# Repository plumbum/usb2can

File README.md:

usb2can
=======

USB/Serial to CAN bus converter

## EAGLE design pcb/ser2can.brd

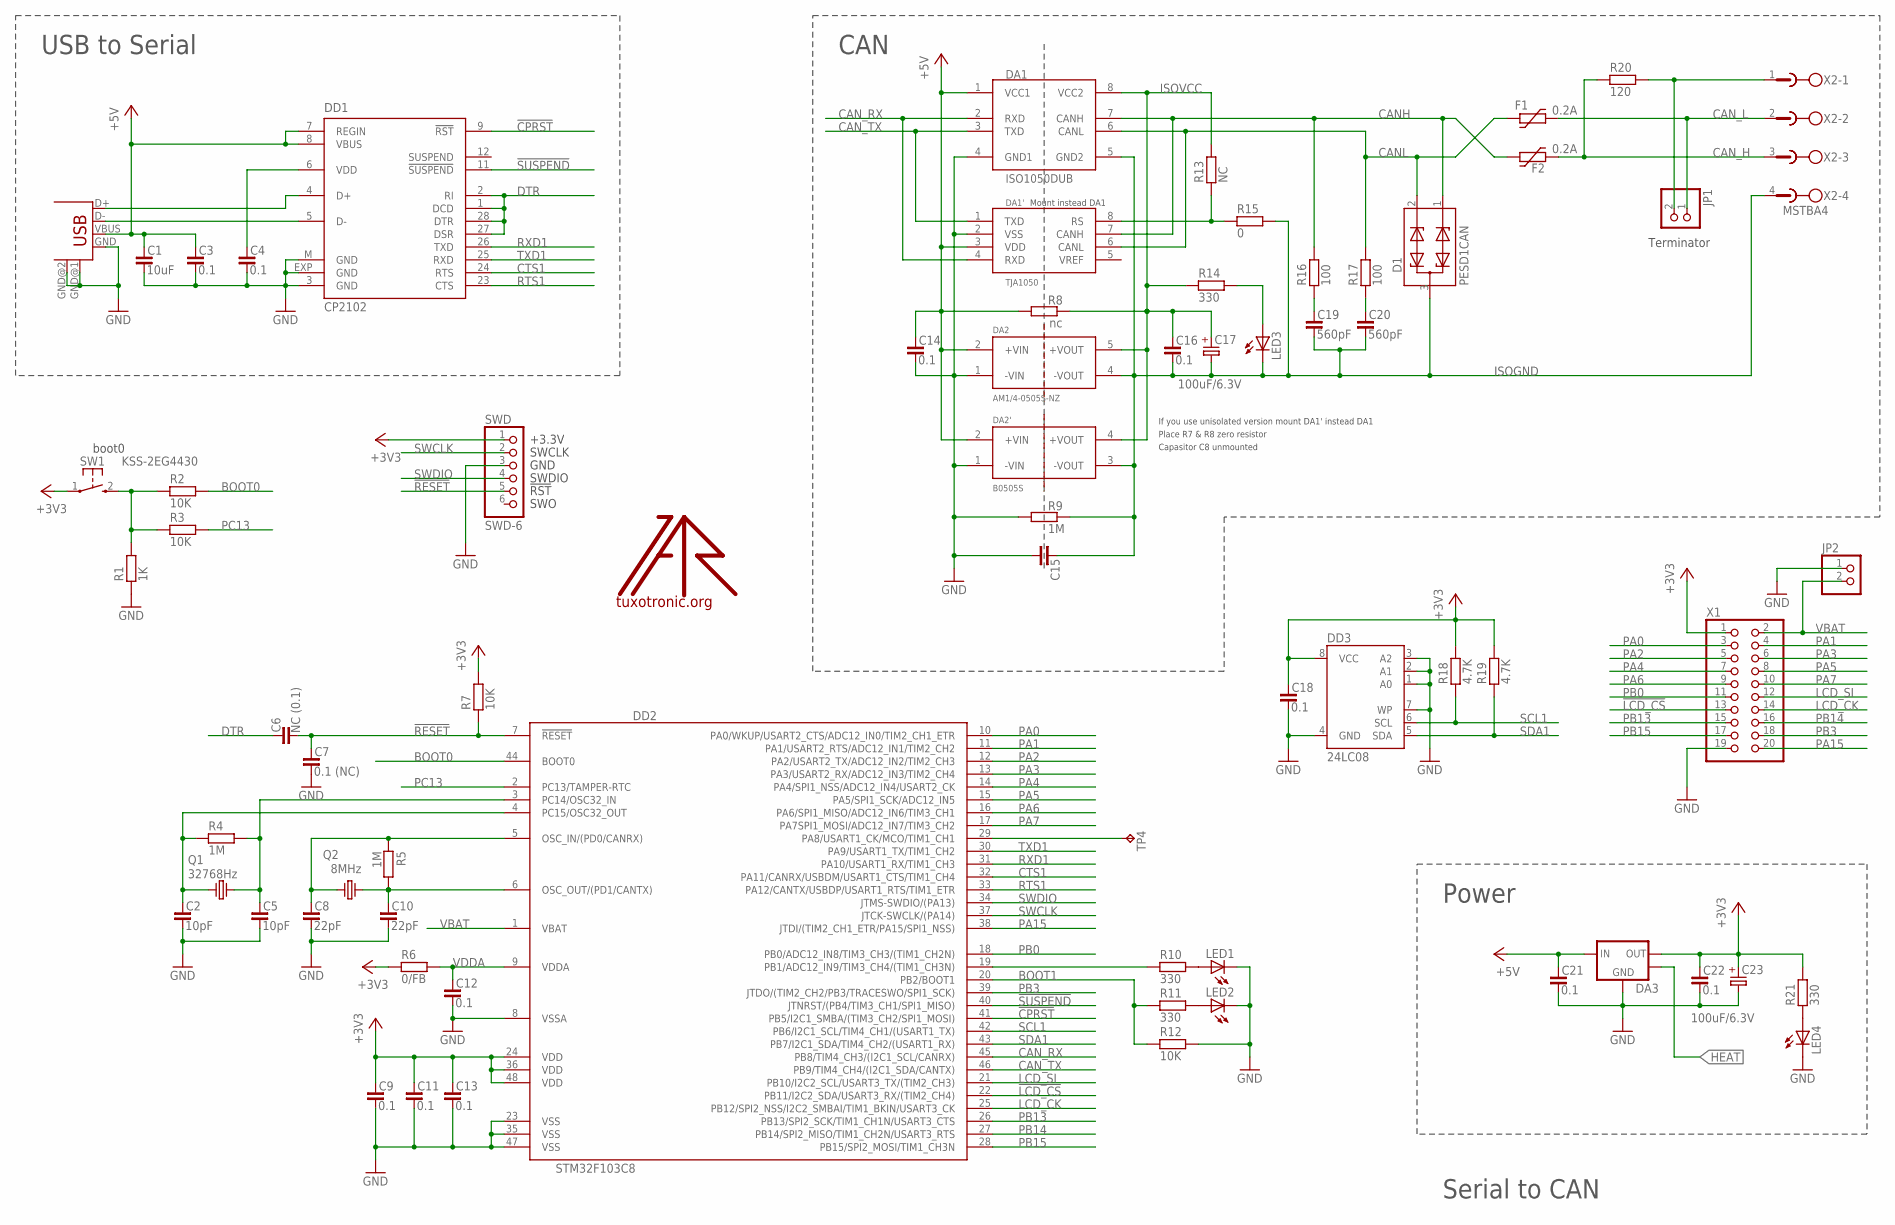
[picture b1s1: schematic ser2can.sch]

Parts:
C1: 10uF; C0603
C2, C5: 10pF; C0603
C3, C4, C9, C11, C12, C13, C14, C16, C18: 0.1; C0603
C6: NC (0.1); C0603
C7: 0.1 (NC); C0603
C8, C10: 22pF; C0603
C15: C_C050-110X055; C050-110X055
C17, C23: 100uF/6.3V; SMC_C
C19, C20: 560pF; C0603
C21, C22: 0.1; C0805
D1: PESD1CAN; SOT23
DA1: ISO1050DUB; DUB-8
DA1': TJA1050; SO08
DA2: AM1/4-0505S-NZ; AM1/4
DA2': B0505S; SIP4
DA3: LM1117-3.3; SOT223
DD1: CP2102; MLP28
DD2: STM32F103C8; LQFP48
DD3: 24LC08; SO08
F1, F2: 0.2A; 1812L
JP1: PINHD-1X2_2.54S; 1X02SMALL
JP2: PINHD-1X2_2.00; 1X02M
LED1, LED2, LED3, LED4: LEDCHIPLED_0805; CHIPLED_0805
Q1: 32768Hz; MM20SS
Q2: 8MHz; HC49/S
R1: 1K; R0603
R2, R3, R7, R12: 10K; R0603
R4, R5: 1M; R0603
R6: 0/FB; R0603
R8: nc; R1206
R9: 1M; R1206
R10, R11, R14, R21: 330; R0603
R13: NC; R0603
R15: 0; R0603
R16, R17: 100; R0603
R18, R19: 4.7K; R0603
R20: 120; R0805
SW1: KSS-2EG4430
SWD: SWD-6; JTAG6PIN
TP4: TPB1,27; B1,27
U$: LOGO; TT_LOGO
USB1: USB-B-H
X1: PINHD-2X10_2.54; 2X10
X2: MSTBA4

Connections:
!CPRST: DD1.9 (!RST), DD2.41 (PB5/I2C1_SMBA/(TIM3_CH2/SPI1_MOSI))
!LCD_CS: DD2.22 (PB11/I2C2_SDA/USART3_RX/(TIM2_CH4)), X1.13
!RESET: C6.2, C7.1, DD2.7 (!RESET), R7.1, SWD.5
!SUSPEND: DD1.11 (!SUSPEND), DD2.40 (JTNRST/(PB4/TIM3_CH1/SPI1_MISO))
+3V3: C9.1, C11.1, C13.1, C18.1, C22.1, C23.+, DA3.2 (OUT), DD2.24 (VDD), DD2.36 (VDD), DD2.48 (VDD), DD3.8 (VCC), R6.1, R7.2, R18.2, R19.2, R21.2, SW1.1, SWD.1, X1.1
+5V: C1.1, C3.1, C14.1, C21.1, DA1.1 (VCC1), DA1'.3 (VDD), DA2.2 (+VIN), DA2'.2 (+VIN), DA3.3 (IN), DD1.7 (REGIN), DD1.8 (VBUS), R8.1, USB1.VBUS
BOOT0: DD2.44 (BOOT0), R2.2
BOOT1: DD2.20 (PB2/BOOT1), R11.1, R12.1
CANH: D1.1, DA1.7 (CANH), DA1'.7 (CANH), F2.P$1 (1), R16.2
CANL: D1.2, DA1.6 (CANL), DA1'.6 (CANL), F1.P$1 (1), R17.2
CAN_H: F2.P$2 (2), R20.1, X2.3
CAN_L: F1.P$2 (2), JP1.1, X2.2
CAN_L_R: JP1.2, R20.2, X2.1
CAN_RX: DA1.2 (RXD), DA1'.4 (RXD), DD2.45 (PB8/TIM4_CH3/(I2C1_SCL/CANRX))
CAN_TX: DA1.3 (TXD), DA1'.1 (TXD), DD2.46 (PB9/TIM4_CH4/(I2C1_SDA/CANTX))
CTS1: DD1.24 (RTS), DD2.32 (PA11/CANRX/USBDM/USART1_CTS/TIM1_CH4)
DTR: C6.1, DD1.1 (DCD), DD1.2 (RI), DD1.27 (DSR), DD1.28 (DTR)
GND: C1.2, C2.2, C3.2, C4.2, C5.2, C7.2, C8.2, C9.2, C10.2, C11.2, C12.2, C13.2, C14.2, C15.2, C18.2, C21.2, C22.2, C23.-, DA1.4 (GND1), DA1'.2 (VSS), DA2.1 (-VIN), DA2'.1 (-VIN), DA3.1 (GND), DD1.3 (GND), DD1.EXP (GND), DD1.M (GND), DD2.8 (VSSA), DD2.23 (VSS), DD2.35 (VSS), DD2.47 (VSS), DD3.1 (A0), DD3.2 (A1), DD3.3 (A2), DD3.4 (GND), DD3.7 (WP), JP2.1, LED1.C, LED2.C, LED4.C, R1.1, R9.1, R12.2, SWD.3, USB1.GND, USB1.GND@1 (GND), USB1.GND@2 (GND), X1.19
HEAT: DA3.4 (MASS)
ISOGND: C15.1, C16.2, C17.-, C19.2, C20.2, D1.3, DA1.5 (GND2), DA2.4 (-VOUT), DA2'.3 (-VOUT), LED3.C, R9.2, R15.2, X2.4
ISOVCC: C16.1, C17.+, DA1.8 (VCC2), DA2.5 (+VOUT), DA2'.4 (+VOUT), R8.2, R13.2, R14.1
LCD_CK: DD2.25 (PB12/SPI2_NSS/I2C2_SMBAI/TIM1_BKIN/USAR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), X1.14
LCD_SI: DD2.21 (PB10/I2C2_SCL/USART3_TX/(TIM2_CH3)), X1.12
unnamed: R1.2, R2.1, R3.1, SW1.2 (S)
unnamed: DD2.29 (PA8/USART1_CK/MCO/TIM1_CH1), TP4.PP
unnamed: LED2.A, R11.2
unnamed: LED1.A, R10.2
unnamed: LED3.A, R14.2
unnamed: DD1.5 (D-), USB1.D-
unnamed: DD1.4 (D+), USB1.D+
unnamed: LED4.A, R21.1
unnamed: DD2.19 (PB1/ADC12_IN9/TIM3_CH4/(TIM1_CH3N)), R10.1
unnamed: DA1'.8 (RS), R13.1, R15.1
unnamed: C4.1, DD1.6 (VDD)
unnamed: C20.1, R17.1
unnamed: C19.1, R16.1
OSC_IN: C8.1, DD2.5 (OSC_IN/(PD0/CANRX)), Q2.1, R5.1
OSC_IN1: C5.1, DD2.3 (PC14/OSC32_IN), Q1.4 (2), R4.2
OSC_OUT: C10.1, DD2.6 (OSC_OUT/(PD1/CANTX)), Q2.2, R5.2
OSC_OUT1: C2.1, DD2.4 (PC15/OSC32_OUT), Q1.1, R4.1
PA0: DD2.10 (PA0/WKUP/USART2_CTS/ADC12_IN0/TIM2_CH1_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), X1.3
PA1: DD2.11 (PA1/USART2_RTS/ADC12_IN1/TIM2_CH2), X1.4
PA2: DD2.12 (PA2/USART2_TX/ADC12_IN2/TIM2_CH3), X1.5
PA3: DD2.13 (PA3/USART2_RX/ADC12_IN3/TIM2_CH4), X1.6
PA4: DD2.14 (PA4/SPI1_NSS/ADC12_IN4/USART2_CK), X1.7
PA5: DD2.15 (PA5/SPI1_SCK/ADC12_IN5), X1.8
PA6: DD2.16 (PA6/SPI1_MISO/ADC12_IN6/TIM3_CH1), X1.9
PA7: DD2.17 (PA7SPI1_MOSI/ADC12_IN7/TIM3_CH2), X1.10
PA15: DD2.38 (JTDI/(TIM2_CH1_ETR/PA15/SPI1_NSS)), X1.20
PB0: DD2.18 (PB0/ADC12_IN8/TIM3_CH3/(TIM1_CH2N)), X1.11
PB3: DD2.39 (JTDO/(TIM2_CH2/PB3/TRACESWO/SPI1_SCK)), X1.18
PB13: DD2.26 (PB13/SPI2_SCK/TIM1_CH1N/USART3_CTS), X1.15
PB14: DD2.27 (PB14/SPI2_MISO/TIM1_CH2N/USART3_RTS), X1.16
PB15: DD2.28 (PB15/SPI2_MOSI/TIM1_CH3N), X1.17
PC13: DD2.2 (PC13/TAMPER-RTC), R3.2
RTS1: DD1.23 (CTS), DD2.33 (PA12/CANTX/USBDP/USART1_RTS/TIM1_ETR)
RXD1: DD1.26 (TXD), DD2.31 (PA10/USART1_RX/TIM1_CH3)
SCL1: DD2.42 (PB6/I2C1_SCL/TIM4_CH1/(USART1_TX)), DD3.6 (SCL), R18.1
SDA1: DD2.43 (PB7/I2C1_SDA/TIM4_CH2/(USART1_RX)), DD3.5 (SDA), R19.1
SWCLK: DD2.37 (JTCK-SWCLK/(PA14)), SWD.2
SWDIO: DD2.34 (JTMS-SWDIO/(PA13)), SWD.4
TXD1: DD1.25 (RXD), DD2.30 (PA9/USART1_TX/TIM1_CH2)
VBAT: DD2.1 (VBAT), JP2.2, X1.2
VDDA: C12.1, DD2.9 (VDDA), R6.2

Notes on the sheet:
CAN
Serial to CAN
USB to Serial
Power
boot0
Mount instead DA1
If you use unisolated version mount DA1' instead DA1
Place R7 & R8 zero resistor
Capasitor C8 unmounted
Terminator

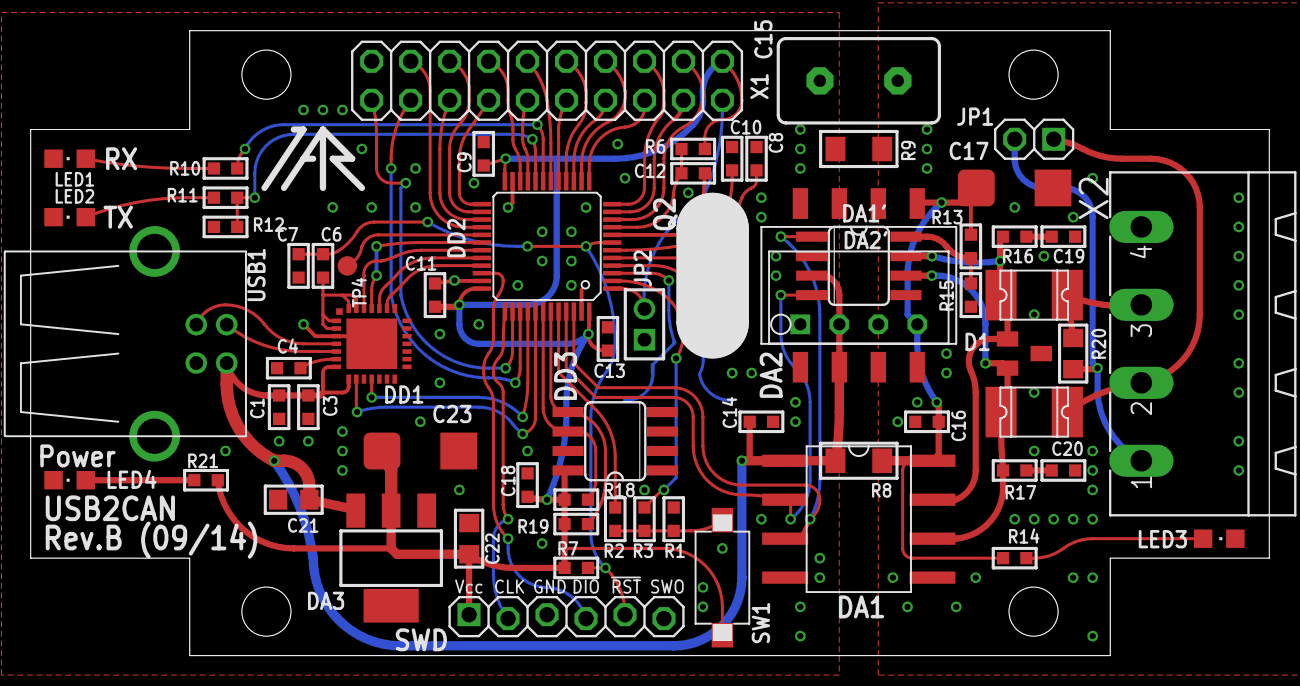
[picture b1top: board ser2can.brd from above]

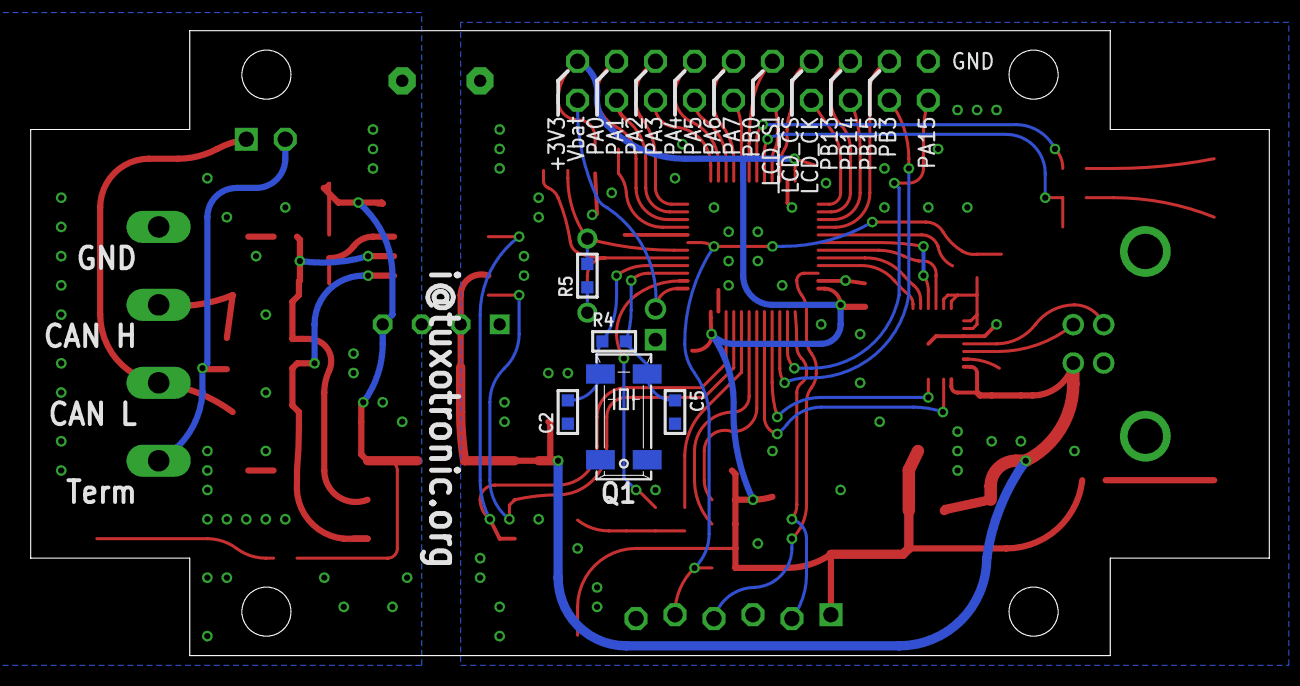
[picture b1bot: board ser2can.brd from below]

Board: 2 copper layers, 80.7 x 40.7 mm, 70 parts (5 on the bottom side), 63 nets.

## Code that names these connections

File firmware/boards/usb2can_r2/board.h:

/*
    ChibiOS - Copyright (C) 2006..2015 Giovanni Di Sirio

    Licensed under the Apache License, Version 2.0 (the "License");
    you may not use this file except in compliance with the License.
    You may obtain a copy of the License at

        http://www.apache.org/licenses/LICENSE-2.0

    Unless required by applicable law or agreed to in writing, software
    distributed under the License is distributed on an "AS IS" BASIS,
    WITHOUT WARRANTIES OR CONDITIONS OF ANY KIND, either express or implied.
    See the License for the specific language governing permissions and
    limitations under the License.
*/

#ifndef _BOARD_H_
#define _BOARD_H_

/*
 * Setup for the STM32F103C8T6 Module often described as "Arduino"-like
 * on eBay, typically marked "www.vcc-gnd.com".
 */

/*
 * Board identifier.
 */
#define BOARD_USB2CAN_R2
#define BOARD_NAME              "USB2CAN (via serial)"

/*
 * Board frequencies.
 */
#define STM32_LSECLK            32768
#define STM32_HSECLK            8000000

/*
 * MCU type, supported types are defined in ./os/hal/platforms/hal_lld.h.
 *
 * Only xB (128KB Flash) is defined, but it's identical to the
 * x8 version (64KB Flash) except for the Flash region size in the
 * linker script. For x8 parts use xB here and change to the x8 linker
 * script in the project Makefile.
 */
#define STM32F103xB

/*
 * IO pins assignments
 *
 * numbering is sorted by onboard/connectors, as from the schematics in
 * http://www.vcc-gnd.com/read.php?tid=369
 */

/* on-board */

#define GPIOB_LED1      1
#define GPIOB_LED2      2
#define SetLed1()       palSetPad(GPIOB, GPIOB_LED1);
#define ClrLed1()       palClearPad(GPIOB, GPIOB_LED1);
#define ToggleLed1()    palTogglePad(GPIOB, GPIOB_LED1);
#define SetLed2()       palSetPad(GPIOB, GPIOB_LED2);
#define ClrLed2()       palClearPad(GPIOB, GPIOB_LED2);
#define ToggleLed2()    palTogglePad(GPIOB, GPIOB_LED2);

#define GPIOC_BUTTON 13
#define GetButton() (GPIOC & (1<<GPIOC_BUTTON))

// #define GPIOA_USBDM             11      // pin 8
// #define GPIOA_USBDP             12      // pin 9

// #define GPIOC_OSC32_IN          14
// #define GPIOC_OSC32_OUT         15

/*
 * I/O ports initial setup, this configuration is established soon after reset
 * in the initialization code.
 *
 * The digits have the following meaning:
 *   0 - Analog input.
 *   1 - Push Pull output 10MHz.
 *   2 - Push Pull output 2MHz.
 *   3 - Push Pull output 50MHz.
 *   4 - Digital input.
 *   5 - Open Drain output 10MHz.
 *   6 - Open Drain output 2MHz.
 *   7 - Open Drain output 50MHz.
 *   8 - Digital input with PullUp or PullDown resistor depending on ODR.
 *   9 - Alternate Push Pull output 10MHz.
 *   A - Alternate Push Pull output 2MHz.
 *   B - Alternate Push Pull output 50MHz.
 *   C - Reserved.
 *   D - Alternate Open Drain output 10MHz.
 *   E - Alternate Open Drain output 2MHz.
 *   F - Alternate Open Drain output 50MHz.
 * Please refer to the STM32 Reference Manual for details.
 */

/*
 * Port A setup.
 * Everything input with pull-up except:
 * PA9  - TXD1
 * PA10 - RXD1
 * PA11 - CTS1
 * PA12 - RTS1
 * PA13 - SWDIO
 * PA14 - SWCLK
 */
#define VAL_GPIOACRL            0x88888888      /*  PA7...PA0 */
#define VAL_GPIOACRH            0x888388B8      /* PA15...PA8 */
#define VAL_GPIOAODR            0xFFFFFFFF

/*
 * Port B setup.
 * Everything input with pull-up except:
 * PB1  - LED1
 * PB2  - LED2
 * PB4  - #SUSPEND
 * PB5  - #CPRST
 * PB6  - SCL1
 * PB7  - SDA1
 * PB8  - CAN_RX
 * PB9  - CAN_TX
 * PB10 - LCD_SI
 * PB11 - #LCD_CS
 * PB12 - LCD_CK
 */
#define VAL_GPIOBCRL            0xFF888338      /*  PB7...PB0 */
#define VAL_GPIOBCRH            0x888B3BB8      /* PB15...PB8 */
#define VAL_GPIOBODR            (0xFFFFFFFF & ~(1<<GPIOB_LED1) & ~(1<<GPIOB_LED2))

/*
 * Port C setup.
 * Everything input with pull-up except:
 * PC13 - Digital input (BUTTON).
 */
#define VAL_GPIOCCRL            0x88888888      /*  PC7...PC0 */
#define VAL_GPIOCCRH            0x44488888      /* PC15...PC8 */
#define VAL_GPIOCODR            (0xFFFFFFFF & ~(1<<GPIOC_BUTTON))

/*
 * Port D setup.
 * Everything input with pull-up except:
 * PD0  - Normal input (XTAL).
 * PD1  - Normal input (XTAL).
 */
#define VAL_GPIODCRL            0x88888844      /*  PD7...PD0 */
#define VAL_GPIODCRH            0x88888888      /* PD15...PD8 */
#define VAL_GPIODODR            0xFFFFFFFF

/*
 * Port E setup.
 * Everything input with pull-up except:
 */
#define VAL_GPIOECRL            0x88888888      /*  PE7...PE0 */
#define VAL_GPIOECRH            0x88888888      /* PE15...PE8 */
#define VAL_GPIOEODR            0xFFFFFFFF

/*
 * USB bus activation macro, required by the USB driver.
 */
#define usb_lld_connect_bus(usbp)	/* always connected */

/*
 * USB bus de-activation macro, required by the USB driver.
 */
#define usb_lld_disconnect_bus(usbp)	/* always connected */

#if !defined(_FROM_ASM_)
#ifdef __cplusplus
extern "C" {
#endif
  void boardInit(void);
#ifdef __cplusplus
}
#endif
#endif /* _FROM_ASM_ */

#endif /* _BOARD_H_ */

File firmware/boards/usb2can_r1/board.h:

/*
    ChibiOS/RT - Copyright (C) 2006-2013 Giovanni Di Sirio

    Licensed under the Apache License, Version 2.0 (the "License");
    you may not use this file except in compliance with the License.
    You may obtain a copy of the License at

        http://www.apache.org/licenses/LICENSE-2.0

    Unless required by applicable law or agreed to in writing, software
    distributed under the License is distributed on an "AS IS" BASIS,
    WITHOUT WARRANTIES OR CONDITIONS OF ANY KIND, either express or implied.
    See the License for the specific language governing permissions and
    limitations under the License.
*/

#ifndef _BOARD_H_
#define _BOARD_H_

/*
 * Setup for the Olimex STM32-P103 proto board.
 */

#define DES_FSIZE ((uint16_t*)0x1FFFF7E0)
#define U_ID      ((uint32_t*)0x1FFFF7E8)

/*
 * Board identifier.
 */
#define BOARD_USB2CAN_R1
#define BOARD_NAME              "USB(Serial) to CAN converter, Rev.A"

/*
 * Board frequencies.
 */
#define STM32_LSECLK            32768
#define STM32_HSECLK            8000000

/*
 * MCU type, supported types are defined in ./os/hal/platforms/hal_lld.h.
 */
#define STM32F10X_MD

/*
 * IO pins assignments.
 */
#define GPIOB_LED1              2
#define GPIOB_LED2              1

/*
 * I/O ports initial setup, this configuration is established soon after reset
 * in the initialization code.
 *
 * The digits have the following meaning:
 *   0 - Analog input.
 *   1 - Push Pull output 10MHz.
 *   2 - Push Pull output 2MHz.
 *   3 - Push Pull output 50MHz.
 *   4 - Digital input.
 *   5 - Open Drain output 10MHz.
 *   6 - Open Drain output 2MHz.
 *   7 - Open Drain output 50MHz.
 *   8 - Digital input with PullUp or PullDown resistor depending on ODR.
 *   9 - Alternate Push Pull output 10MHz.
 *   A - Alternate Push Pull output 2MHz.
 *   B - Alternate Push Pull output 50MHz.
 *   C - Reserved.
 *   D - Alternate Open Drain output 10MHz.
 *   E - Alternate Open Drain output 2MHz.
 *   F - Alternate Open Drain output 50MHz.
 * Please refer to the STM32 Reference Manual for details.
 */

/*
 * Port A setup.
 * Everything input with pull-up except:
 * PA8  - Alternate output  (MCO).
 * PA9  - Alternate output  (USART1 TX).
 * PA10 - Normal input      (USART1 RX).
 * PA11 - Normal input      (USART1 CTS).
 * PA12 - Push Pull output  (USART1 RTS).
 */
#define VAL_GPIOACRL            0x88888888      /*  PA7...PA0 */
#define VAL_GPIOACRH            0x888B88BB      /* PA15...PA8 */
#define VAL_GPIOAODR            0xFFFFFFFF

/*
 * Port B setup.
 * Everything input with pull-up except:
 * PB1  - Push Pull output  (LED2 green)
 * PB2  - Push Pull output  (LED1 red)
 * PB4  - Normal input      (USB !SUSPEND).
 * PB5  - Push Pull output  (USB !RESET)
 * PB6  - Alternate Open Drain  (I2C1 SCL)
 * PB7  - Alternate Open Drain  (I2C1 SDA)
 * PB8  - Normal input      (CAN RX).
 * PB9  - Alternate output  (CAN TX).
 * PB10 - Alternate output  (LCD MOSI / USART3 TX).
 * PB10 - Push Pull output  (!LCD CS / USART3 RX).
 * PB10 - Alternate output  (LCD SCK / USART3 CK).
 * PB13 - Alternate output  (MMC SPI2 SCK).
 * PB14 - Normal input      (MMC SPI2 MISO).
 * PB15 - Alternate output  (MMC SPI2 MOSI).
 */
#define VAL_GPIOBCRL            0xFF388338      /*  PB7...PB0 */
#define VAL_GPIOBCRH            0xB8BB3BB8      /* PB15...PB8 */
#define VAL_GPIOBODR            0xFFFFFFFF

/*
 * Port C setup.
 * Everything input with pull-up except:
 */
#define VAL_GPIOCCRL            0x88888888      /*  PC7...PC0 */
#define VAL_GPIOCCRH            0x88888888      /* PC15...PC8 */
#define VAL_GPIOCODR            0xFFFFFFFF

/*
 * Port D setup.
 * Everything input with pull-up except:
 * PD0  - Normal input (XTAL).
 * PD1  - Normal input (XTAL).
 */
#define VAL_GPIODCRL            0x88888844      /*  PD7...PD0 */
#define VAL_GPIODCRH            0x88888888      /* PD15...PD8 */
#define VAL_GPIODODR            0xFFFFFFFF

/*
 * Port E setup.
 * Everything input with pull-up except:
 */
#define VAL_GPIOECRL            0x88888888      /*  PE7...PE0 */
#define VAL_GPIOECRH            0x88888888      /* PE15...PE8 */
#define VAL_GPIOEODR            0xFFFFFFFF

/*
 * USB bus activation macro, required by the USB driver.
 */
#define usb_lld_connect_bus(usbp) palClearPad(GPIOC, GPIOC_USB_DISC)

/*
 * USB bus de-activation macro, required by the USB driver.
 */
#define usb_lld_disconnect_bus(usbp) palSetPad(GPIOC, GPIOC_USB_DISC)

#if !defined(_FROM_ASM_)
#ifdef __cplusplus
extern "C" {
#endif
  void boardInit(void);
#ifdef __cplusplus
}
#endif
#endif /* _FROM_ASM_ */

#endif /* _BOARD_H_ */

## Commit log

2013-02-08 PCB Rev.A, git ignore files
2013-05-03 pcb rev.b
2013-05-03 Test application
2013-05-03 pcb fix sizes, addition elements
2013-05-30 sample firmware
2013-05-30 status led routines
2013-05-30 shell test
2013-05-30 copy chibios shell files
2013-05-30 customize shell
2013-12-21 battery additional pads
2013-12-21 cityhash test
2014-07-03 serial to can translator
2014-07-03 ChibiOS 2.6.5 now use
2014-07-03 about can filters
2014-07-03 misprints fixes
2014-07-04 sch&pcb some modifications
2014-09-04 contribute sources
2014-09-05 little changes. pictures
2014-09-05 show image in readme (test)
2014-09-08 Add alternative DC-DC B0505S-1W (MornSun, etc)
2017-01-24 update ChibiOs to 16.1.6, skeleton app, vscode
2017-01-25 upload and lock via openocd
2017-01-25 ignore build directory
2017-01-25 howto selfprotect firmware
2017-01-25 mircrorl - readline library
2017-01-25 microrl config changes
2017-01-25 use baudrate 115200
2017-01-25 rename task load to upload
2017-01-25 wrap make commands
2017-01-25 try uart, chibi shell and microrl (readline)
2017-01-27 skeleton: custom shell for CANhacker
2017-01-31 commands skell
2017-01-31 copy of protocol description. Unformated
2017-02-01 Move CAN function to different files
